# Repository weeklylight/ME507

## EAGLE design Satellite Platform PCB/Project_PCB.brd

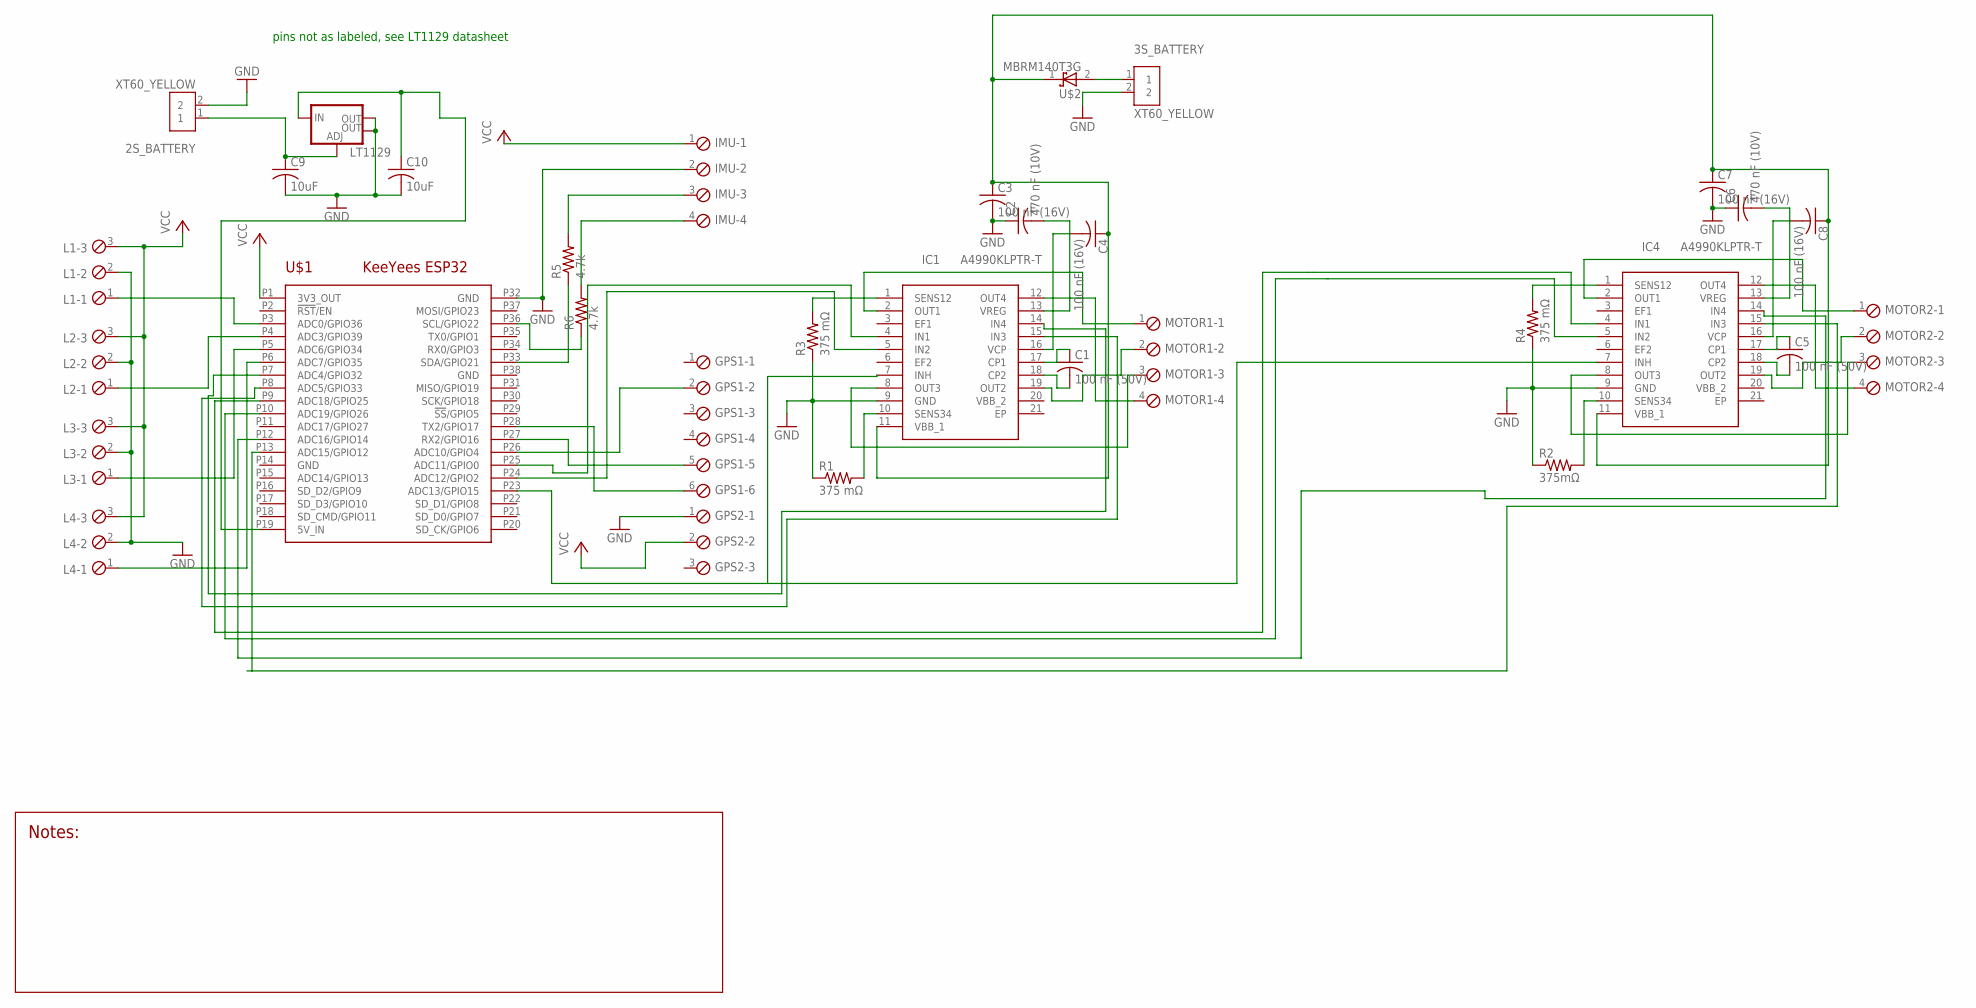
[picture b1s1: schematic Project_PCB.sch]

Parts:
2S_BATTERY, 3S_BATTERY: XT60_YELLOW; AMASS_XT60PB-M
C1, C5: 100 nF (50V); C0805
C2, C6: 470 nF (10V); C0805
C3, C4, C7, C8: 100 nF (16V); C0805
C9, C10: 10uF; C0805
GPS1: SCREWTERM_6P_254; 6POL254
GPS2: SCREWTERM_3P_254; 3POL254
IC1, IC4: A4990KLPTR-T; A4405KLPTRT
IMU: SCREWTERM_6P_254; 6POL254
L1, L2, L3, L4: SCREWTERM_3P_254; 3POL254
LT1129: V_REG_LM1117SOT223; SOT223
MOTOR1, MOTOR2: SCREWTERM_4P_254; 4POL254
R1, R3, R4: 375 mΩ; R0805
R2: 375mΩ; R0805
R5, R6: 4.7k; R0805
U$1: KEEYEES_ESP32
U$2: MBRM140T3G; DIO_MBRM110LT1G

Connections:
GND: 2S_BATTERY.2, 3S_BATTERY.2, C2.1, C3.2, C6.1, C7.2, C9.2, C10.2, GPS2.1, IC1.9 (GND), IC4.9 (GND), IMU.2, L1.2, L2.2, L3.2, L4.2, LT1129.2 (OUT), LT1129.4 (OUT), R1.1, R2.1, R3.1, R4.1, U$1.P14 (GND), U$1.P32 (GND), U$1.P38 (GND)
unnamed: C10.1, LT1129.3 (IN), U$1.P19 (5V_IN)
unnamed: GPS1.6, U$1.P28 (TX2/GPIO17)
unnamed: 3S_BATTERY.1, U$2.2 (A)
unnamed: L1.1, U$1.P3 (ADC0/GPIO36)
unnamed: GPS1.2, U$1.P26 (ADC10/GPIO4)
unnamed: GPS1.5, U$1.P27 (RX2/GPIO16)
unnamed: L2.1, U$1.P4 (ADC3/GPIO39)
unnamed: L3.1, U$1.P5 (ADC6/GPIO34)
unnamed: L4.1, U$1.P6 (ADC7/GPIO35)
unnamed: IMU.3, R5.2
unnamed: IMU.4, R6.2
unnamed: C1.1, IC1.17 (CP1)
unnamed: C1.2, IC1.18 (CP2)
unnamed: IC1.12 (OUT4), MOTOR1.4
unnamed: IC1.2 (OUT1), MOTOR1.1
unnamed: IC1.19 (OUT2), MOTOR1.2
unnamed: IC1.8 (OUT3), MOTOR1.3
unnamed: C4.2, IC1.16 (VCP)
unnamed: IC1.10 (SENS34), R1.2
unnamed: IC1.1 (SENS12), R3.2
unnamed: C3.1, C4.1, C7.1, C8.1, IC1.11 (VBB_1), IC4.11 (VBB_1), U$2.1 (C)
unnamed: C2.2, IC1.13 (VREG)
unnamed: IC1.4 (IN1), U$1.P25 (ADC11/GPIO0)
unnamed: IC1.5 (IN2), U$1.P24 (ADC12/GPIO2)
unnamed: IC1.7 (INH), IC4.7 (INH), U$1.P23 (ADC13/GPIO15)
unnamed: IC1.14 (IN4), U$1.P7 (ADC4/GPIO32)
unnamed: IC1.15 (IN3), U$1.P8 (ADC5/GPIO33)
unnamed: C5.1, IC4.17 (CP1)
unnamed: C5.2, IC4.18 (CP2)
unnamed: IC4.12 (OUT4), MOTOR2.4
unnamed: IC4.2 (OUT1), MOTOR2.1
unnamed: IC4.19 (OUT2), MOTOR2.2
unnamed: IC4.8 (OUT3), MOTOR2.3
unnamed: IC4.10 (SENS34), R2.2
unnamed: IC4.1 (SENS12), R4.2
unnamed: R6.1, U$1.P36 (SCL/GPIO22)
unnamed: C8.2, IC4.16 (VCP)
unnamed: C6.2, IC4.13 (VREG)
unnamed: IC4.4 (IN1), U$1.P9 (ADC18/GPIO25)
unnamed: IC4.5 (IN2), U$1.P10 (ADC19/GPIO26)
unnamed: R5.1, U$1.P33 (SDA/GPIO21)
unnamed: IC4.14 (IN4), U$1.P12 (ADC16/GPIO14)
unnamed: IC4.15 (IN3), U$1.P13 (ADC15/GPIO12)
unnamed: 2S_BATTERY.1, C9.1, LT1129.1 (ADJ)
VCC: GPS2.2, IMU.1, L1.3, L2.3, L3.3, L4.3, U$1.P1 (3V3_OUT)

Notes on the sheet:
pins not as labeled, see LT1129 datasheet

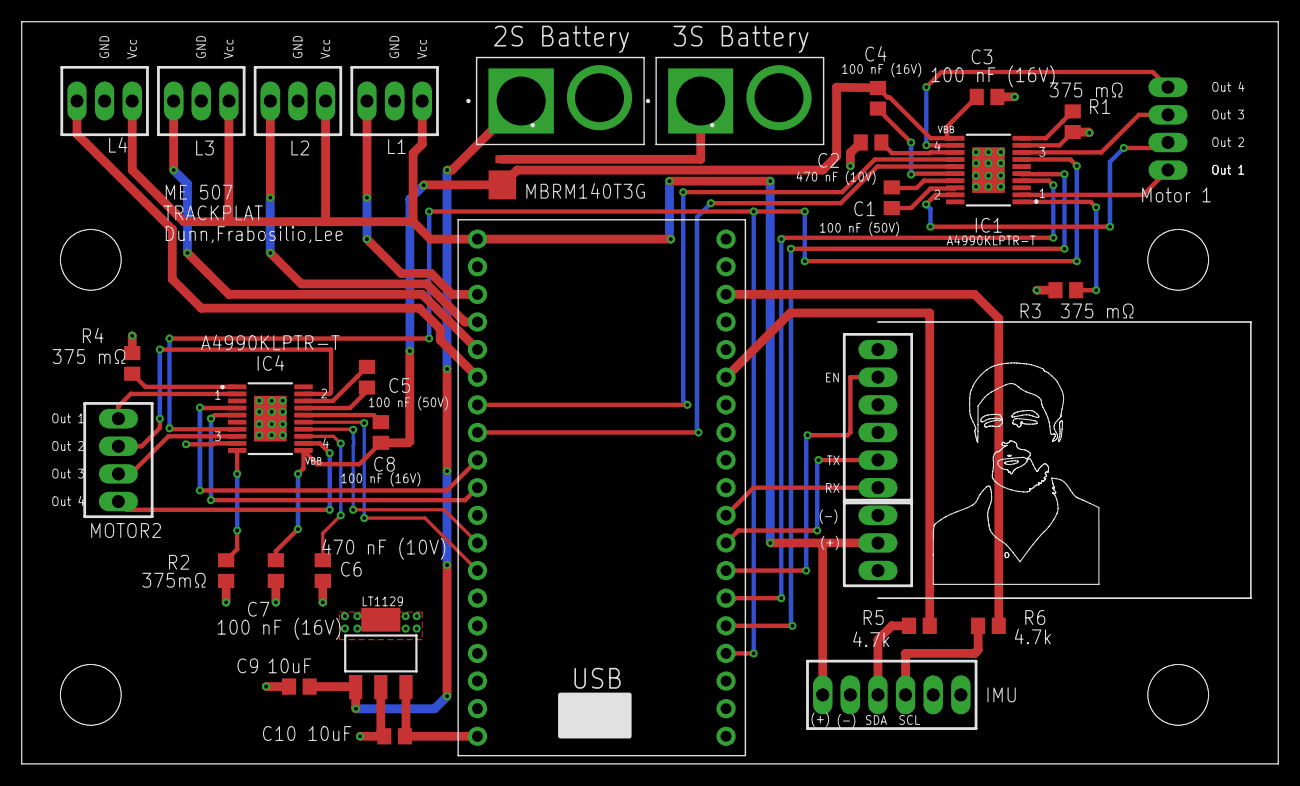
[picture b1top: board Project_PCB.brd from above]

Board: 2 copper layers, 115.5 x 68.2 mm, 32 parts (1 on the bottom side), 46 nets.

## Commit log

2022-10-13 Added a test script
2022-10-13 VS code initial commit
    created VS code project
2022-10-13 Uploading Schematic Files
2022-10-13 Rearranged PCB files
2022-10-13 deleted old test files
2022-10-13 added libraries to vs code
2022-10-13 Finished wiring schematic
2022-10-16 Attached enable pins together
2022-10-16 Added diode
2022-10-16 Added all last names to title block
2022-10-16 Added R and C values
2022-10-16 added board
    airwires still
2022-10-20 Added testing code for IMU and Motor Driver
2022-10-20 rewired
    updated based on ridgely's comments
2022-10-24 Finished wiring
    still need names layer
2022-10-24 Added Pin Labels
2022-10-26 Fixed names
    moved all names to tnames layer, noted orientation of motor driver chips, organized labels
2022-10-27 Added heat sinks to motors
2022-10-27 approved DRC errors
2022-10-27 gerber folder made
2022-10-27 Got motor driver working
2022-10-27 pcb gerber
2022-10-27 Added limit switch test code
2022-10-27 tried fixing crank
    didnt work
2022-10-27 track plat bottom added
2022-10-28 fixed zip folder
2022-11-01 Worked on code
2022-11-03 Testing
2022-11-03 Removed Folder
2022-11-03 Included Folder
2022-11-03 Setup basic shares and queues
2022-11-03 Worked on GPS and IMU tasks
2022-11-17 IMU class
    IMU class
2022-11-17 Testing motor driver test
2022-11-17 motor_crtl
    updates to imu class
2022-11-23 Testing with pcb motor driver
2022-11-24 GPS works, motor gets data from position and imu
2022-11-24 Got server working
2022-11-26 stls
    updated stl
2022-11-26 Revert "Merge branch 'main' of https://github.com/weeklylight/ME507"
    This reverts commit ffc93c0d5a7ae6936d80dc627667bb3c75a1ff8d, reversing
    changes made to a84cca885dddae96950d6709d376336046812fab.
2022-11-26 adding imu functionality to main
    work in progress. Adding memory to imu task fixes crashes
2022-11-26 Revert "adding imu functionality to main"
    This reverts commit e5df8c1d7f87e2443ee7e29d55b520bb37085e25.
2022-11-26 Revert "Revert "Merge branch 'main' of https://github.com/weeklylight/ME507""
    This reverts commit 15a67d78a99114938a1740bd04f7f034590cef95.
2022-11-26 IMU Functionality
    fixed reversion issues and added IMU support. motor doesn't behave as desired, but only activates when imu tilts
2022-11-28 Doxygen comments
    Added Doxygen comments for Imu class
2022-11-30 Officially working
2022-12-01 Update main.cpp
    updated limit switches and started SIV task
2022-12-01 Alex's testing
2022-12-01 balance
    as it should be
2022-12-01 Revert "Merge branch 'main' of https://github.com/weeklylight/ME507"
    This reverts commit 3dc2306dd72f6fd4a8f234a9fe4e64b65f318a5f, reversing
    changes made to cf75c9a0640f1a025b87844b86af80fd92a7bb8a.
2022-12-01 Revert "ff"
    This reverts commit cf75c9a0640f1a025b87844b86af80fd92a7bb8a.
2022-12-01 Working software
2022-12-01 final commit
2022-12-04 Adding doxygen comments
2022-12-04 Finished Alex's doxygen stuff
2022-12-06 Added functionality to enable/disable simple platform leveling
2022-12-07 commmented SIV optimiser
2022-12-07 testing doxygen
2022-12-07 Moved docs folder
2022-12-22 Cleaning up

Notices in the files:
parts and their libraries:
SparkFun-IC-Power: Licensing: Creative Commons ShareAlike 4.0 International - https://creativecommons.org/licenses/by-sa/4.0
